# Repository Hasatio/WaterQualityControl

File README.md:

# Water Quality Control

The circuit taken as an example while designing the board [Adafruit PCA9685](https://www.adafruit.com/product/815)

## Revision 0

### Added:

- 1x TCA9406 (Voltage Level Translator)
- 2x ADS1115 (Analog to Digital Converter)
- 1x MCP23008 (I/O Expander)
- 3x DRV8870 (Motor Driver)
- 1x K7805-2000R3L or K7805-2000R3 for 5V supply
- 2x QWIIC connector

### Changed:

- Logo

### Updates:

- 2x Step motor driver

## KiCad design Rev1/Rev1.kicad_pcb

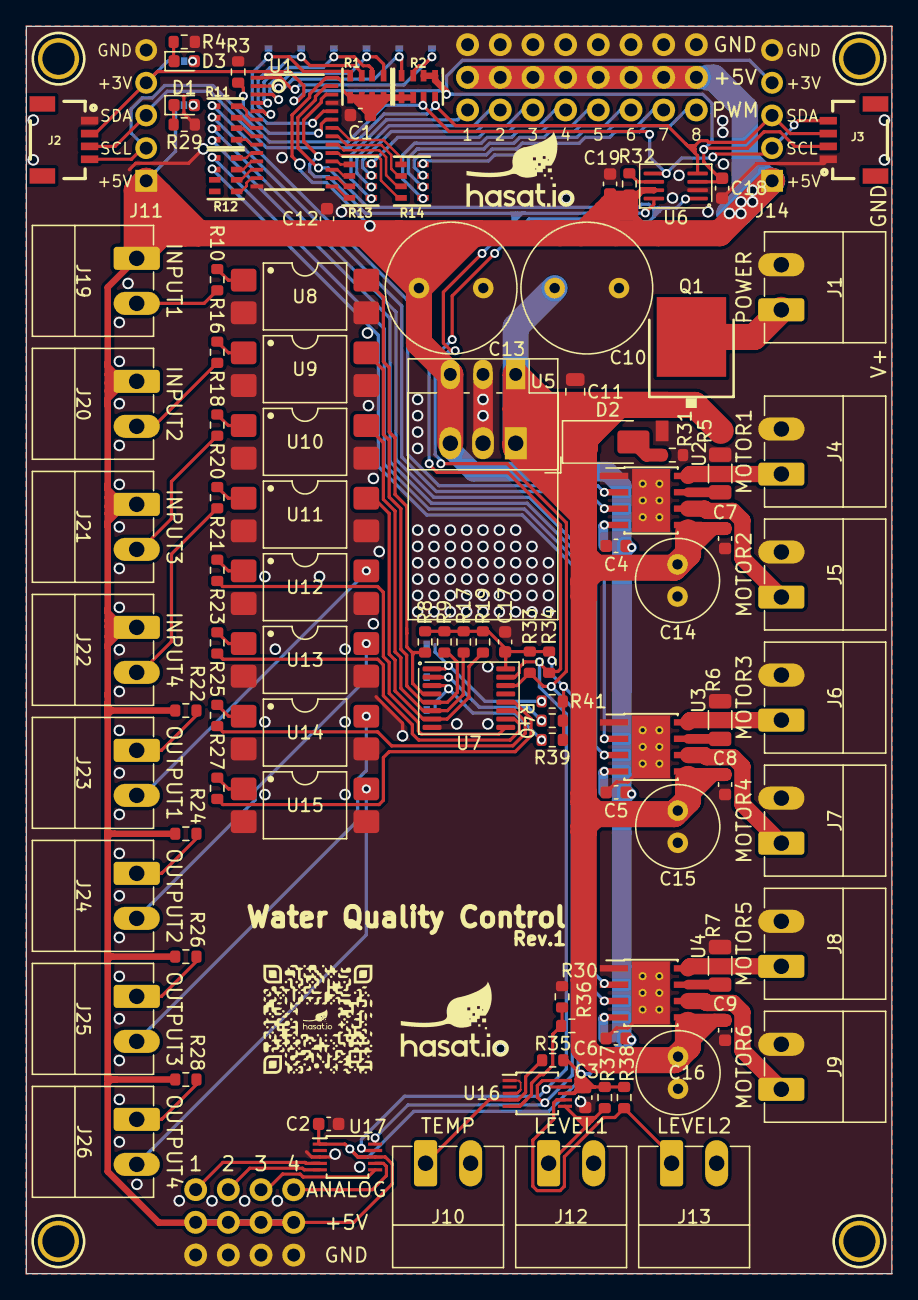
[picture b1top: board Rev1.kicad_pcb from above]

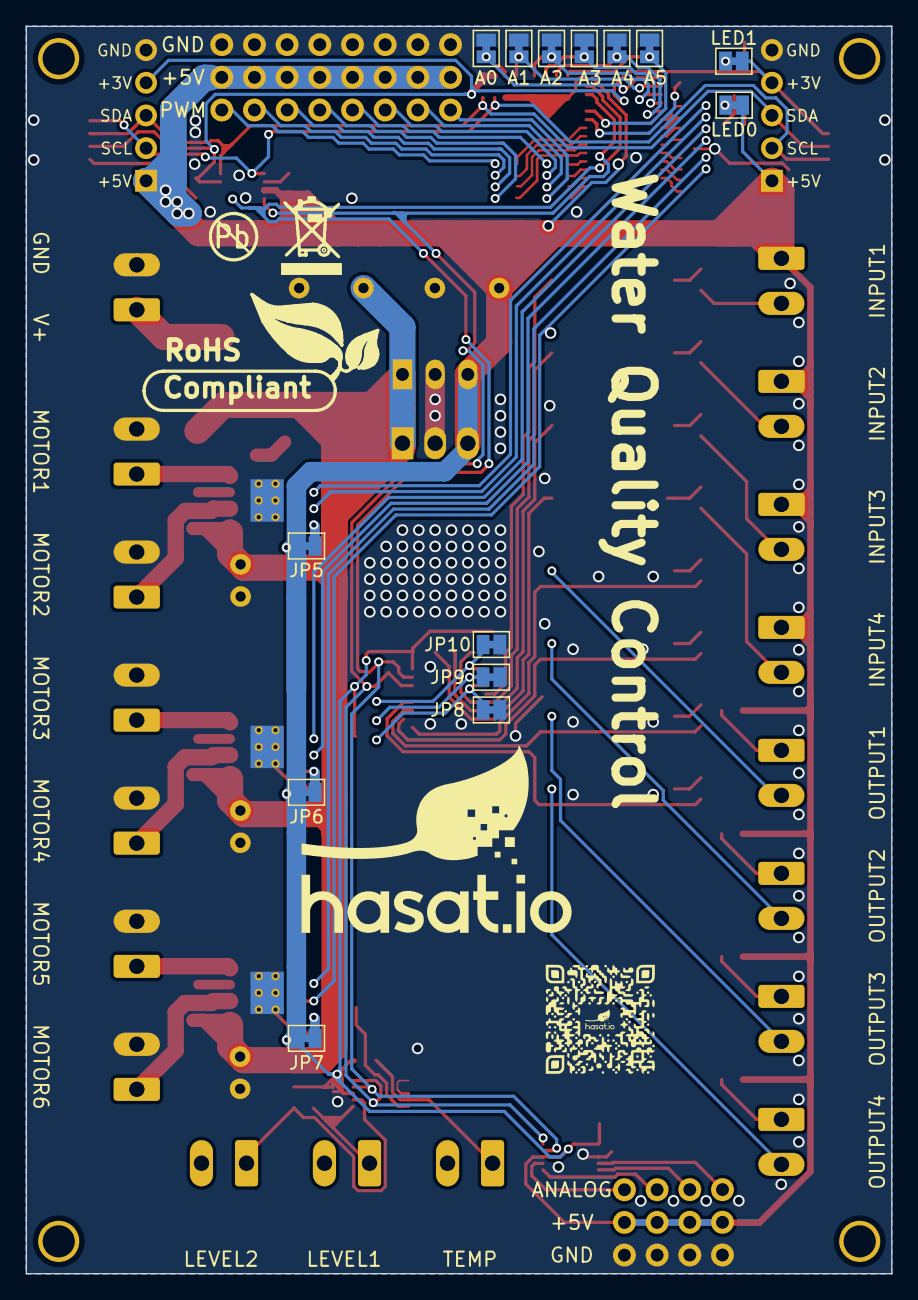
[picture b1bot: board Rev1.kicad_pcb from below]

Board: 2 copper layers, 67.3 x 96.9 mm, 129 parts (17 on the bottom side), 103 nets.

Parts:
A0, A1, A2, A3, A4, A5: SolderJumper_2_Bridged; SolderJumper-2_P1.3mm_Bridged_Pad1.0x1.5mm
C1, C2, C3, C4, C5, C6, C17, C18, C19: 0.1uF; C_0603_1608Metric
C7, C8, C9: 0.1uF/35v; C_0603_1608Metric
C10, C13: 1000uF/35v; C_Radial_D10.0mm_H20.0mm_P5.00mm
C11: 10uF/100v; C_0805_2012Metric
C12: 10uF; C_0603_1608Metric
C14, C15, C16: 47uF/35v; C_Radial_D6.3mm_H11.0mm_P2.50mm
D1: GREEN; LED_0603_1608Metric
D2: Z1SMA4740; D_SMA
D3: RED; LED_0603_1608Metric
J1, J4, J5, J6, J7, J8, J9, J10, J12, J13, J19, J20, J21, J22, J23, J24, J25, J26: TERMBLOCK_1X2; PhoenixContact_MC_1,5_2-G-3.5_1x02_P3.50mm_Horizontal
J2, J3: QWIIC_RIGHT_ANGLE; 1X04_1MM_RA_STRESSRELIEF
J11, J14: Conn_01x05; PinHeader_1x05_P2.54mm_Vertical
JP1, JP2, JP12, JP13, JP14, JP15: Header 2x3; 3X02
JP5, JP6, JP7, JP8, JP9, JP10: SolderJumper_2_Bridged; SolderJumper-2_P1.3mm_Bridged_Pad1.0x1.5mm
LED0, LED1: SolderJumper_2_Bridged; SolderJumper-2_P1.3mm_Bridged_Pad1.0x1.5mm
Q1: AOD417; TO252
R1, R2: 10k/603x4; RESPACK_4X0603
R3, R8, R9, R17, R19, R32, R33, R34, R36, R39, R40, R41: 10K; R_0603_1608Metric
R4: 1k; R_0603_1608Metric
R5, R6, R7: 250m/1w; R_1206_3216Metric
R10, R16, R18, R20: 750R; R_0603_1608Metric
R11, R12, R13, R14: 220R/603x4; RESPACK_4X0603
R21, R23, R25, R27: 380R; R_0603_1608Metric
R22, R24, R26, R28: 100R; R_0603_1608Metric
R29: 2k2; R_0603_1608Metric
R30: 2K; R_0603_1608Metric
R31: 100k; R_0603_1608Metric
R35, R37, R38: 270R; R_0603_1608Metric
Sign-RecyclBin: LOGO_RECYCLEBIN_1
Sign_Pb-Free: LOGO_PBFREE
Sign_RoHS: Val**; LOGO_ROHS_1
U1: PCA9685; TSSOP28
U2, U3, U4: DRV8870DDA; Texas_HTSOP-8-1EP_3.9x4.9mm_P1.27mm_EP2.95x4.9mm_Mask2.4x3.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
U5: K7805-2000R3L; Converter_DCDC_RECOM_R-78HB-0.5L_THT
U6: TCA9406DC; SSOP-8_2.95x2.8mm_P0.65mm
U7: TCA9534; TSSOP-16_4.4x5mm_P0.65mm
U8, U9, U10, U11, U12, U13, U14, U15: LTV-817S; SMDIP-4_W9.53mm
U16, U17: ADS1115IDGS; TSSOP-10_3x3mm_P0.5mm
U$47, U$48, U$49: MOUNTINGHOLE2.5; MOUNTINGHOLE_2.5_PLATED
U$e: MOUNTINGHOLE2.5; MOUNTINGHOLE_2.5_PLATED

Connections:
+3.3V: C18.1, J2.2, J3.2, J11.4, J14.4, LED1.1 (A), R2.5 (2), R2.6 (2), U6.3 (VCCA)
+5V: C1.1, C2.1, C3.1, C4.1, C5.1, C6.1, C12.1, C13.1, C17.1, C19.1, J11.1, J14.1, J19.1, J20.1, J21.1, J22.1, JP1.2, JP1.5, JP2.2, JP2.5, JP5.1 (A), JP6.1 (A), JP7.1 (A), JP12.2, JP12.5, JP13.2, JP13.5, JP14.2, JP14.5, JP15.2, JP15.5, LED0.1 (A), R1.1, R1.2 (1), R1.3 (1), R1.4 (1), R2.1, R2.2 (1), R8.2, R9.2, R17.2, R19.2, R22.2, R24.2, R26.2, R28.2, R32.1, R33.1, R34.1, R35.1, R37.1, R38.1, R39.2, R40.2, R41.2, U1.28 (VDD), U5.3 (OUT), U6.7 (VCCB), U7.16 (VDD), U16.8 (VDD), U17.1 (ADDR), U17.8 (VDD)
/A0: A0.1 (A), R2.7 (2), U1.1 (A0)
/A0_1: JP8.1 (A), R39.1, U7.3 (A2)
/A1: A1.1 (A), R2.8 (2), U1.2 (A1)
/A1_1: JP9.1 (A), R40.1, U7.2 (A1)
/A2: A2.1 (A), R1.5 (2), U1.3 (A2)
/A2_1: JP10.1 (A), R41.1, U7.1 (A0)
/A3: A3.1 (A), R1.6 (2), U1.4 (A3)
/A4: A4.1 (A), R1.7 (2), U1.5 (A4)
/A5: A5.1 (A), R1.8 (2), U1.24 (A5)
/Ain0: J10.1, R35.2, U16.4 (AIN0)
/Ain1: R30.1, R36.2, U16.5 (AIN1)
/Ain2: J12.1, R37.2, U16.6 (AIN2)
/Ain3: J13.1, R38.2, U16.7 (AIN3)
/Ain4: JP2.3, U17.4 (AIN0)
/Ain5: JP2.6, U17.5 (AIN1)
/Ain6: JP1.3, U17.6 (AIN2)
/Ain7: JP1.6, U17.7 (AIN3)
/I0: J19.2, R10.2
/I1: J20.2, R16.2
/I2: J21.2, R18.2
/I3: J22.2, R20.2
/In0: R8.1, U7.4 (P0), U8.4
/In1: R9.1, U7.5 (P1), U9.4
/In2: R17.1, U7.6 (P2), U10.4
/In3: R19.1, U7.7 (P3), U11.4
/O0A: J23.1, R22.1
/O0B: J23.2, U12.4
/O1A: J24.1, R24.1
/O1B: J24.2, U13.4
/O2A: J25.1, R26.1
/O2B: J25.2, U14.4
/O3A: J26.1, R28.1
/O3B: J26.2, U15.4
/Out0: R21.2, U7.9 (P4)
/Out1: R23.2, U7.10 (P5)
/Out2: R25.2, U7.11 (P6)
/Out3: R27.2, U7.12 (P7)
/P0: R11.5 (2), U2.2 (IN2)
/P1: R11.6 (2), U2.3 (IN1)
/P2: R11.7 (2), U3.2 (IN2)
/P3: R11.8 (2), U3.3 (IN1)
/P4: R12.5 (2), U4.2 (IN2)
/P5: R12.6 (2), U4.3 (IN1)
/P8: JP12.1, R13.5 (2)
/P9: JP12.4, R13.6 (2)
/P10: JP13.1, R13.7 (2)
/P11: JP13.4, R13.8 (2)
/P12: JP14.1, R14.5 (2)
/P13: JP14.4, R14.6 (2)
/P14: JP15.1, R14.7 (2)
/P15: JP15.4, R14.8 (2)
/PWM0: R11.4 (1), U1.6 (PWM0)
/PWM1: R11.3 (1), U1.7 (PWM1)
/PWM2: R11.2 (1), U1.8 (PWM2)
/PWM3: R11.1, U1.9 (PWM3)
/PWM4: R12.4 (1), U1.10 (PWM4)
/PWM5: R12.3 (1), U1.11 (PWM5)
/PWM6: R12.2 (1), U1.12 (PWM6)
/PWM7: R12.1, U1.13 (PWM7)
/PWM8: R13.4 (1), U1.15 (PWM8)
/PWM9: R13.3 (1), U1.16 (PWM9)
/PWM10: R13.2 (1), U1.17 (PWM10)
/PWM11: R13.1, U1.18 (PWM11)
/PWM12: R14.4 (1), U1.19 (PWM12)
/PWM13: R14.3 (1), U1.20 (PWM13)
/PWM14: R14.2 (1), U1.21 (PWM14)
/PWM15: R14.1, U1.22 (PWM15)
/SCL_A: J2.4, J3.4, J11.2, J14.2, R2.3 (1), U6.5 (SCL_A)
/SCL_B: R33.2, U1.26 (SCL), U6.8 (SCL_B), U7.14 (SCL), U16.10 (SCL), U17.10 (SCL)
/SDA_A: J2.3, J3.3, J11.3, J14.3, R2.4 (1), U6.4 (SDA_A)
/SDA_B: R34.2, U1.27 (SDA), U6.1 (SDA_B), U7.15 (SDA), U16.9 (SDA), U17.9 (SDA)
GND: A0.2 (B), A1.2 (B), A2.2 (B), A3.2 (B), A4.2 (B), A5.2 (B), C1.2, C2.2, C3.2, C4.2, C5.2, C6.2, C7.2, C8.2, C9.2, C10.2, C11.2, C12.2, C13.2, C14.2, C15.2, C16.2, C17.2, C18.2, C19.2, J1.2, J2.1, J3.1, J4.2, J5.2, J6.2, J7.2, J8.2, J9.2, J11.5, J14.5, JP1.1, JP1.4, JP2.1, JP2.4, JP8.2 (B), JP9.2 (B), JP10.2 (B), JP12.3, JP12.6, JP13.3, JP13.6, JP14.3, JP14.6, JP15.3, JP15.6, Q1.1 (G), R3.1, R4.2, R5.1, R6.1, R7.1, R29.2, R30.2, R31.1, U1.14 (GND), U1.25 (EXTCLK), U2.1 (GND), U2.9 (GND), U3.1 (GND), U3.9 (GND), U4.1 (GND), U4.9 (GND), U5.2 (GND), U6.2 (GND), U7.8 (GND), U8.2, U8.3, U9.2, U9.3, U10.2, U10.3, U11.2, U11.3, U12.2, U12.3, U13.2, U13.3, U14.2, U14.3, U15.2, U15.3, U16.1 (ADDR), U16.3 (GND), U17.3 (GND)
unnamed: D1.2 (A), LED0.2 (B)
unnamed: D1.1 (K), R29.1
unnamed: D2.2 (A), R31.2
unnamed: D3.2 (A), LED1.2 (B)
unnamed: D3.1 (K), R4.1
unnamed: JP5.2 (B), U2.4 (VREF)
unnamed: JP6.2 (B), U3.4 (VREF)
unnamed: JP7.2 (B), U4.4 (VREF)
unnamed: J1.1, Q1.3 (D)
unnamed: R10.1, U8.1
unnamed: R16.1, U9.1
unnamed: R18.1, U10.1
unnamed: R20.1, U11.1
unnamed: R21.1, U12.1
unnamed: R23.1, U13.1
unnamed: R25.1, U14.1
unnamed: R27.1, U15.1
unnamed: R3.2, U1.23 (#OE)
unnamed: R5.2, U2.7 (ISEN)
unnamed: J5.1, U2.6 (OUT1)
unnamed: J4.1, U2.8 (OUT2)
unnamed: R6.2, U3.7 (ISEN)
unnamed: J7.1, U3.6 (OUT1)
unnamed: J6.1, U3.8 (OUT2)
unnamed: R7.2, U4.7 (ISEN)
unnamed: J9.1, U4.6 (OUT1)
unnamed: J8.1, U4.8 (OUT2)
unnamed: R32.2, U6.6 (OE)
VCC: C7.1, C8.1, C9.1, C10.1, C11.1, C14.1, C15.1, C16.1, D2.1 (K), Q1.2 (S), R36.1, U2.5 (VM), U3.5 (VM), U4.5 (VM), U5.1 (IN)

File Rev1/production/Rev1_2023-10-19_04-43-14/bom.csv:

Designator,Footprint,Quantity,Value,LCSC Part #
"C1, C12",0603,2,10uF,
"C10, C13",C_Radial_D10.0mm_H20.0mm_P5.00mm,2,1000uF/35v,
C11,0805,1,10uF/100v,
"C14, C15, C16",C_Radial_D6.3mm_H11.0mm_P2.50mm,3,47uF/35v,
"C17, C18, C19, C2, C3, C4, C5, C6",0603,8,0.1uF,
"C7, C8, C9",0603,3,0.1uF/35v,
D1,0603,1,GREEN,
D2,D_SMA,1,Z1SMA4740,
D3,0603,1,RED,
"J1, J10, J12, J13, J19, J20, J21, J22, J23, J24, J25, J26, J4, J5, J6, J7, J8, J9","PhoenixContact_MC_1,5_2-G-3.5_1x02_P3.50mm_Horizontal",18,TERMBLOCK_1X2,
"J2, J3",1X04_1MM_RA_STRESSRELIEF,2,QWIIC_RIGHT_ANGLE,
"J28, J29, J30, J31, J32, J33, J34, J35",PinHeader_1x02_P2.54mm_Vertical,8,Conn_01x02,
"JP1, JP12, JP13, JP14, JP15, JP2",3X02,6,Header 2x3,
"JP3, JP4",1X06-CLEANBIG,2,PINHD-1X6CB,
Q1,TO252,1,AOD417,
"R1, R2",RESPACK_4X0603,2,10k/603x4,
"R10, R15, R17, R19, R3, R32, R33, R34, R36, R8",0603,10,10K,
"R11, R12, R13, R14",RESPACK_4X0603,4,220R/603x4,
"R16, R18, R20, R9",0603,4,750R,
"R21, R23, R25, R27",0603,4,200R,
"R22, R24, R26, R28",0603,4,100R,
"R29, R35, R37, R38, R4",0603,5,1k,
R30,0603,1,2K,
R31,0603,1,100k,
"R5, R6, R7",1206,3,250m/1w,
"SJ_A0, SJ_A1, SJ_A2, SJ_A3, SJ_A4, SJ_A5",SOLDERJUMPER_REFLOW_NOPASTE,6,SOLDERJUMPERREFLOW_NOPASTE,
Sign_Pb-Free,LOGO_PBFREE,1,,
Sign_RoHS,LOGO_ROHS_1,1,Val**,
"TP1, TP2, TP3, TP4, TP5, TP6",TESTPOINT_ROUND_1MM,6,TESTPOINTROUND1MM,
U1,TSSOP28,1,PCA9685,
"U10, U11, U12, U13, U14, U15, U8, U9",DIP-4_W7.62mm_SMDSocket_SmallPads,8,PC817,
"U16, U17",TSSOP-10_3x3mm_P0.5mm,2,ADS1115IDGS,
"U2, U3, U4",Texas_HTSOP-8-1EP_3.9x4.9mm_P1.27mm_EP2.95x4.9mm_Mask2.4x3.1mm_ThermalVias,3,DRV8870DDA,
U5,Converter_DCDC_RECOM_R-78HB-0.5L_THT,1,K7805-2000R3L,
U6,SSOP-8_2.95x2.8mm_P0.65mm,1,TCA9406DC,
U7,SOIC-18W_7.5x11.6mm_P1.27mm,1,MCP23008-xSO,

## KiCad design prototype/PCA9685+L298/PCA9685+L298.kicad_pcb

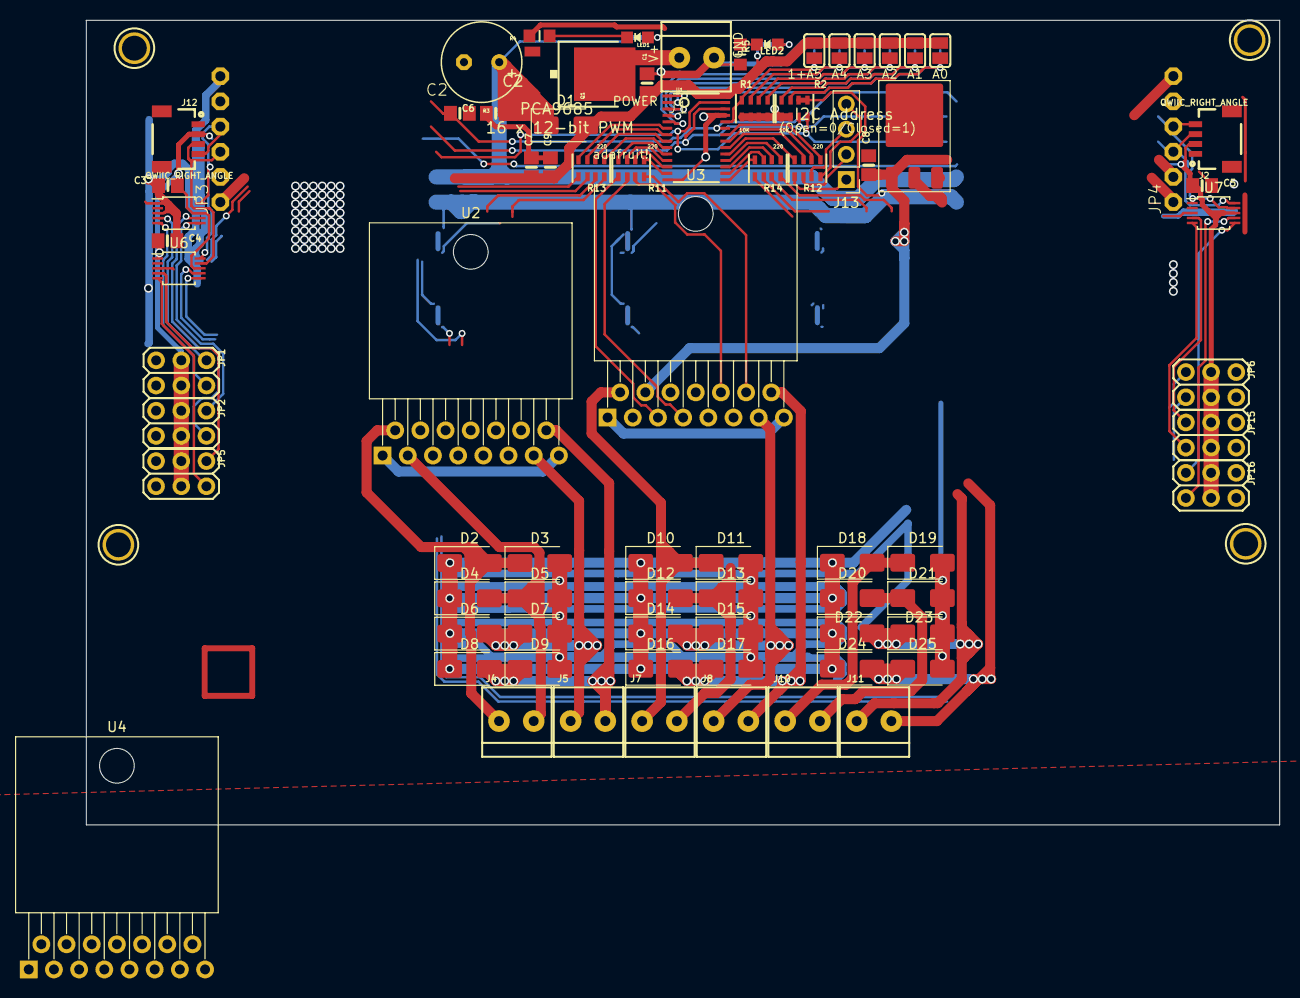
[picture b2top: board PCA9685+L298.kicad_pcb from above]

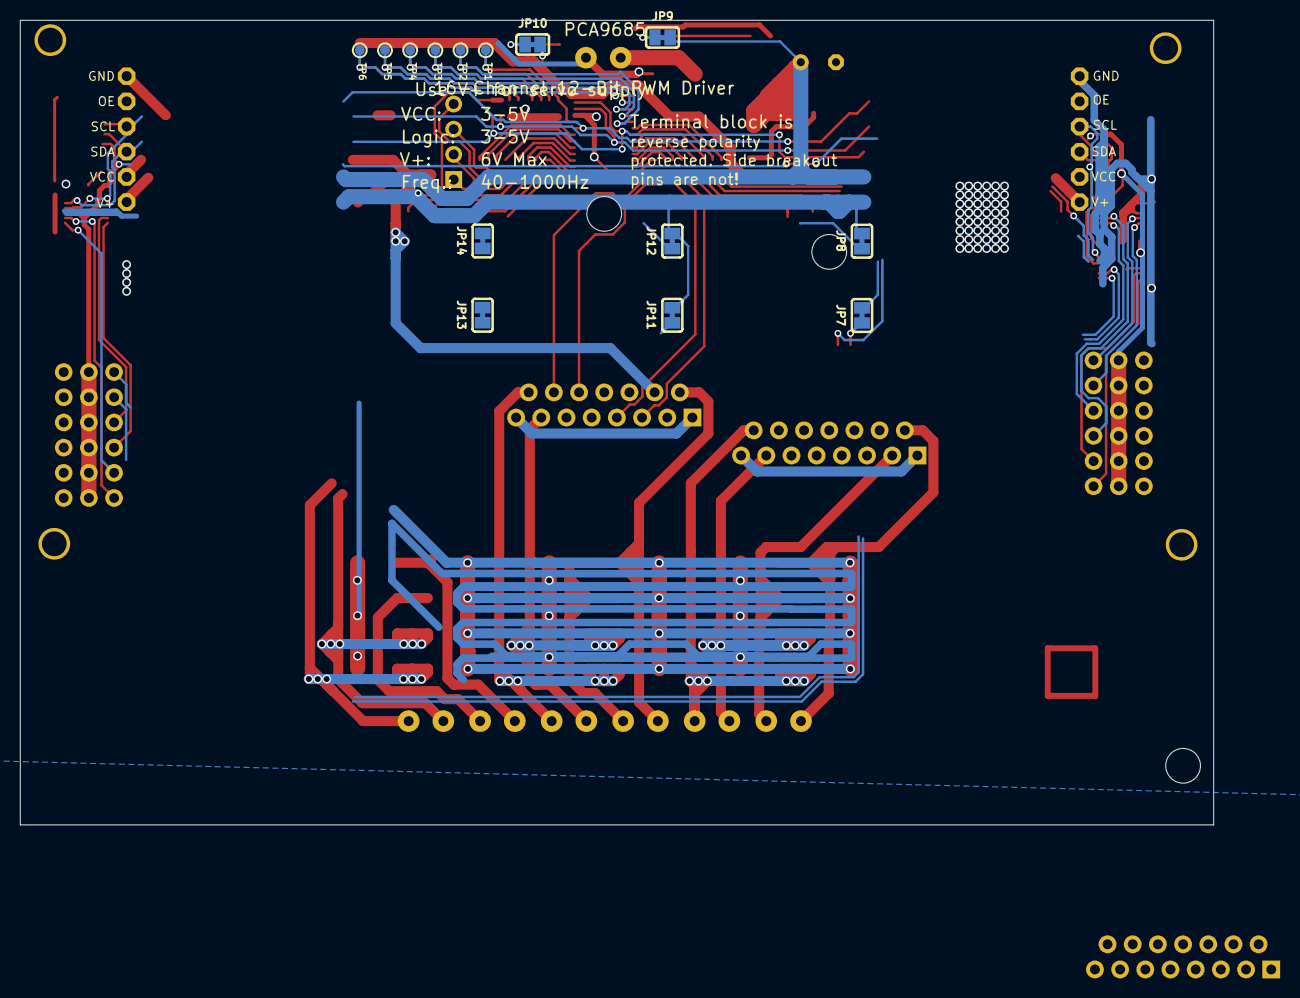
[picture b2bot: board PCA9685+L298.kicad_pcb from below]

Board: 2 copper layers, 120.4 x 81.1 mm, 96 parts (14 on the bottom side), 80 nets.

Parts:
C1, C6, C7: 10uF; 0805-NO
C2: 1000uF; E3,5-8
C3, C4, C5, C8, C9: 1.0uF; 0805-NO
D1, D2, D3, D4, D5, D6, D7, D8, D9, D10, D11, D12, D13, D14, D15, D16, D17, D18, D19, D20, D21, D22, D23, D24, D25: M7; D_SMA
J1, J4, J5, J7, J8, J10, J11: TERMBLOCK_1X2; TERMBLOCK_1X2-3.5MM
J2, J12: QWIIC_RIGHT_ANGLE; 1X04_1MM_RA_STRESSRELIEF
J13: Conn_01x04; PinHeader_1x04_P2.54mm_Vertical
JP1, JP2, JP5, JP6, JP15, JP16: 3X02
JP3, JP4: PINHD-1X6CB; 1X06-CLEANBIG
JP7, JP8, JP9, JP10, JP11, JP12, JP13, JP14: JUMPER-SMT_2_NC_TRACE_SILK; SJ_Closed
LED1: GREEN; CHIPLED_0805_NOOUTLINE
LED2: RED; CHIPLED_0805_NOOUTLINE
Q1: AOD417; TO252
R1, R2: 10K; RESPACK_4X0603
R3: 10K; 0805-NO
R4: 1k; _0805MP
R5: 470; _0805MP
R11, R12, R13, R14: 220; RESPACK_4X0603
SJ_A0, SJ_A1, SJ_A2, SJ_A3, SJ_A4, SJ_A5: SOLDERJUMPERREFLOW_NOPASTE; SOLDERJUMPER_REFLOW_NOPASTE
TP1, TP2, TP3, TP4, TP5, TP6: TESTPOINTROUND1MM; TESTPOINT_ROUND_1MM
U1: PCA9685; TSSOP28
U2, U3, U4: L298HN; TO-220-15_P2.54x2.54mm_StaggerOdd_Lead5.84mm_TabDown
U5, U6, U7: ADS1115IDGS; TSSOP-10_3x3mm_P0.5mm
U8: L7805; TO-252-3_TabPin2
U$47, U$48, U$49, U$50: MOUNTINGHOLE2.5; MOUNTINGHOLE_2.5_PLATED

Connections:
3.3V: C3.1, C4.1, C5.1, J2.2, J12.2, JP1.2, JP1.5, JP2.2, JP2.5, JP5.2, JP5.5, JP6.2, JP6.5, JP15.2, JP15.5, JP16.2, JP16.5, U5.8 (VDD), U6.1 (ADDR), U6.8 (VDD), U7.8 (VDD)
5.0V: C1.1, C7.1, C9.1, D1.2 (A), JP3.1, JP4.1, JP7.2, JP8.2, JP10.2, JP11.2, JP12.2, JP13.2, JP14.2, R2.5 (2), R2.6 (2), SJ_A0.1, SJ_A1.1, SJ_A2.1, SJ_A3.1, SJ_A4.1, SJ_A5.1, U1.28 (VDD), U2.9 (Vss), U3.9 (Vss), U4.9 (Vss), U8.3 (OUT)
/A0: R2.7 (2), SJ_A0.2, TP6.P$1, U1.1 (A0)
/A1: R2.8 (2), SJ_A1.2, TP5.P$1, U1.2 (A1)
/A2: R1.5 (2), SJ_A2.2, TP4.P$1, U1.3 (A2)
/A3: R1.6 (2), SJ_A3.2, TP3.P$1, U1.4 (A3)
/A4: R1.7 (2), SJ_A4.2, TP2.P$1, U1.5 (A4)
/A5: R1.8 (2), SJ_A5.2, TP1.P$1, U1.24 (A5)
/OE: JP3.5, JP4.5, R3.1, U1.23 (#OE)
/P0: R13.5 (2), U2.5 (IN1)
/P1: R13.6 (2), U2.7 (IN2)
/P2: R13.7 (2), U2.10 (IN3)
/P3: R13.8 (2), U2.12 (IN4)
/P4: R11.5 (2), U3.5 (IN1)
/P5: R11.6 (2), U3.7 (IN2)
/P6: R11.7 (2), U3.10 (IN3)
/P7: R11.8 (2), U3.12 (IN4)
/P8: R14.5 (2), U4.5 (IN1)
/P9: R14.6 (2), U4.7 (IN2)
/P10: R14.7 (2), U4.10 (IN3)
/P11: R14.8 (2), U4.12 (IN4)
/PWM0: R13.4 (1), U1.6 (PWM0)
/PWM1: R13.3 (1), U1.7 (PWM1)
/PWM2: R13.2 (1), U1.8 (PWM2)
/PWM3: R13.1, U1.9 (PWM3)
/PWM4: R11.4 (1), U1.10 (PWM4)
/PWM5: R11.3 (1), U1.11 (PWM5)
/PWM6: R11.2 (1), U1.12 (PWM6)
/PWM7: R11.1, U1.13 (PWM7)
/PWM8: R14.4 (1), U1.15 (PWM8)
/PWM9: R14.3 (1), U1.16 (PWM9)
/PWM10: R14.2 (1), U1.17 (PWM10)
/PWM11: R14.1, U1.18 (PWM11)
/PWM12: R12.4 (1), U1.19 (PWM12)
/PWM13: R12.3 (1), U1.20 (PWM13)
/PWM14: R12.2 (1), U1.21 (PWM14)
/PWM15: R12.1, U1.22 (PWM15)
/SCL: J2.4, J12.4, JP3.4, JP4.4, R2.3 (1), U1.26 (SCL), U5.10 (SCL), U6.10 (SCL), U7.1 (ADDR), U7.9 (SDA)
/SDA: J2.3, J12.3, JP3.3, JP4.3, R2.4 (1), U1.27 (SDA), U5.9 (SDA), U6.9 (SDA), U7.10 (SCL)
GND: C1.2, C2.-, C3.2, C4.2, C5.2, C6.2, C7.2, C8.2, C9.2, D3.2 (A), D5.2 (A), D7.2 (A), D9.2 (A), D11.2 (A), D13.2 (A), D15.2 (A), D17.2 (A), D19.2 (A), D21.2 (A), D23.2 (A), D25.2 (A), J1.2, J2.1, J12.1, JP1.1, JP1.4, JP2.1, JP2.4, JP3.6, JP4.6, JP5.1, JP5.4, JP6.3, JP6.6, JP15.3, JP15.6, JP16.3, JP16.6, Q1.1 (G), R1.1, R1.2 (1), R1.3 (1), R1.4 (1), R2.1, R2.2 (1), R3.2, R4.2, R5.2, U1.14 (GND), U1.25 (EXTCLK), U2.1 (SENSE_A), U2.8 (GND), U2.15 (SENSE_B), U3.1 (SENSE_A), U3.8 (GND), U3.15 (SENSE_B), U4.1 (SENSE_A), U4.8 (GND), U4.15 (SENSE_B), U5.1 (ADDR), U5.3 (GND), U6.3 (GND), U7.3 (GND), U8.2 (GND)
unnamed: D2.2 (A), D3.1 (K), J4.2, U2.2 (OUT1)
unnamed: D4.2 (A), D5.1 (K), J4.1, U2.3 (OUT2)
unnamed: D6.2 (A), D7.1 (K), J5.2, U2.13 (OUT3)
unnamed: D8.2 (A), D9.1 (K), J5.1, U2.14 (OUT4)
unnamed: D10.2 (A), D11.1 (K), J7.2, U3.2 (OUT1)
unnamed: D12.2 (A), D13.1 (K), J7.1, U3.3 (OUT2)
unnamed: D14.2 (A), D15.1 (K), J8.2, U3.13 (OUT3)
unnamed: D16.2 (A), D17.1 (K), J8.1, U3.14 (OUT4)
unnamed: D18.2 (A), D19.1 (K), J10.2, U4.2 (OUT1)
unnamed: D20.2 (A), D21.1 (K), J10.1, U4.3 (OUT2)
unnamed: D22.2 (A), D23.1 (K), J11.2, U4.13 (OUT3)
unnamed: D24.2 (A), D25.1 (K), J11.1, U4.14 (OUT4)
unnamed: J13.1, R12.5 (2)
unnamed: J13.2, R12.6 (2)
unnamed: J13.3, R12.7 (2)
unnamed: J13.4, R12.8 (2)
unnamed: JP9.1, LED1.A
unnamed: JP10.1, LED2.A
unnamed: LED1.C, R4.1
unnamed: LED2.C, R5.1
unnamed: J1.1, Q1.3 (D)
unnamed: JP8.1, U2.6 (EnA)
unnamed: JP7.1, U2.11 (EnB)
unnamed: JP12.1, U3.6 (EnA)
unnamed: JP11.1, U3.11 (EnB)
unnamed: JP14.1, U4.6 (EnA)
unnamed: JP13.1, U4.11 (EnB)
unnamed: JP1.3, U5.4 (AIN0)
unnamed: JP1.6, U5.5 (AIN1)
unnamed: JP2.3, U5.6 (AIN2)
unnamed: JP2.6, U5.7 (AIN3)
unnamed: JP5.3, U6.4 (AIN0)
unnamed: JP5.6, U6.5 (AIN1)
unnamed: JP6.1, U6.6 (AIN2)
unnamed: JP6.4, U6.7 (AIN3)
unnamed: JP15.1, U7.4 (AIN0)
unnamed: JP15.4, U7.5 (AIN1)
unnamed: JP16.1, U7.6 (AIN2)
unnamed: JP16.4, U7.7 (AIN3)
VCC: C2.+, C6.1, C8.1, D1.1 (K), D2.1 (K), D4.1 (K), D6.1 (K), D8.1 (K), D10.1 (K), D12.1 (K), D14.1 (K), D16.1 (K), D18.1 (K), D20.1 (K), D22.1 (K), D24.1 (K), JP3.2, JP4.2, JP9.2, Q1.2 (S), U2.4 (Vs), U3.4 (Vs), U4.4 (Vs), U8.1 (IN)

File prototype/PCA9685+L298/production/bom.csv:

Designator,Footprint,Quantity,Value,LCSC Part #
"C1, C6, C7",0805-NO,3,10uF,
C2,"E3,5-8",1,1000uF,
"C3, C4, C5, C8, C9",0805-NO,5,1.0uF,
"D1, D10, D11, D12, D13, D14, D15, D16, D17, D18, D19, D2, D20, D21, D22, D23, D24, D25, D3, D4, D5, D6, D7, D8, D9",D_SMA,25,M7,
"J1, J10, J11, J4, J5, J7, J8",TERMBLOCK_1X2-3.5MM,7,TERMBLOCK_1X2,
"J12, J2",1X04_1MM_RA_STRESSRELIEF,2,QWIIC_RIGHT_ANGLE,
J13,PinHeader_1x04_P2.54mm_Vertical,1,Conn_01x04,
"JP1, JP15, JP16, JP2, JP5, JP6",3X02,6,~,
"JP10, JP11, JP12, JP13, JP14, JP7, JP8, JP9",SJ_Closed,8,JUMPER-SMT_2_NC_TRACE_SILK,
"JP3, JP4",1X06-CLEANBIG,2,PINHD-1X6CB,
LED1,CHIPLED_0805_NOOUTLINE,1,GREEN,
LED2,CHIPLED_0805_NOOUTLINE,1,RED,
Q1,TO252,1,AOD417,
"R1, R2",RESPACK_4X0603,2,10K,
"R11, R12, R13, R14",RESPACK_4X0603,4,220,
R3,0805-NO,1,10K,
R4,_0805MP,1,1k,
R5,_0805MP,1,470,
"SJ_A0, SJ_A1, SJ_A2, SJ_A3, SJ_A4, SJ_A5",SOLDERJUMPER_REFLOW_NOPASTE,6,SOLDERJUMPERREFLOW_NOPASTE,
"TP1, TP2, TP3, TP4, TP5, TP6",TESTPOINT_ROUND_1MM,6,TESTPOINTROUND1MM,
"U$47, U$48, U$49, U$50",MOUNTINGHOLE_2.5_PLATED,4,MOUNTINGHOLE2.5,
U1,TSSOP28,1,PCA9685,
"U2, U3, U4",POWERSO20_L298_PAD,3,L298HN,
"U5, U6, U7",TSSOP-10_3x3mm_P0.5mm,3,ADS1115IDGS,
U8,TO-252-3_TabPin2,1,L7805,

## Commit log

2023-04-18 18.04.23
2023-04-18 rev 0
2023-04-22 23.04.23
2023-04-28 28.04.23
